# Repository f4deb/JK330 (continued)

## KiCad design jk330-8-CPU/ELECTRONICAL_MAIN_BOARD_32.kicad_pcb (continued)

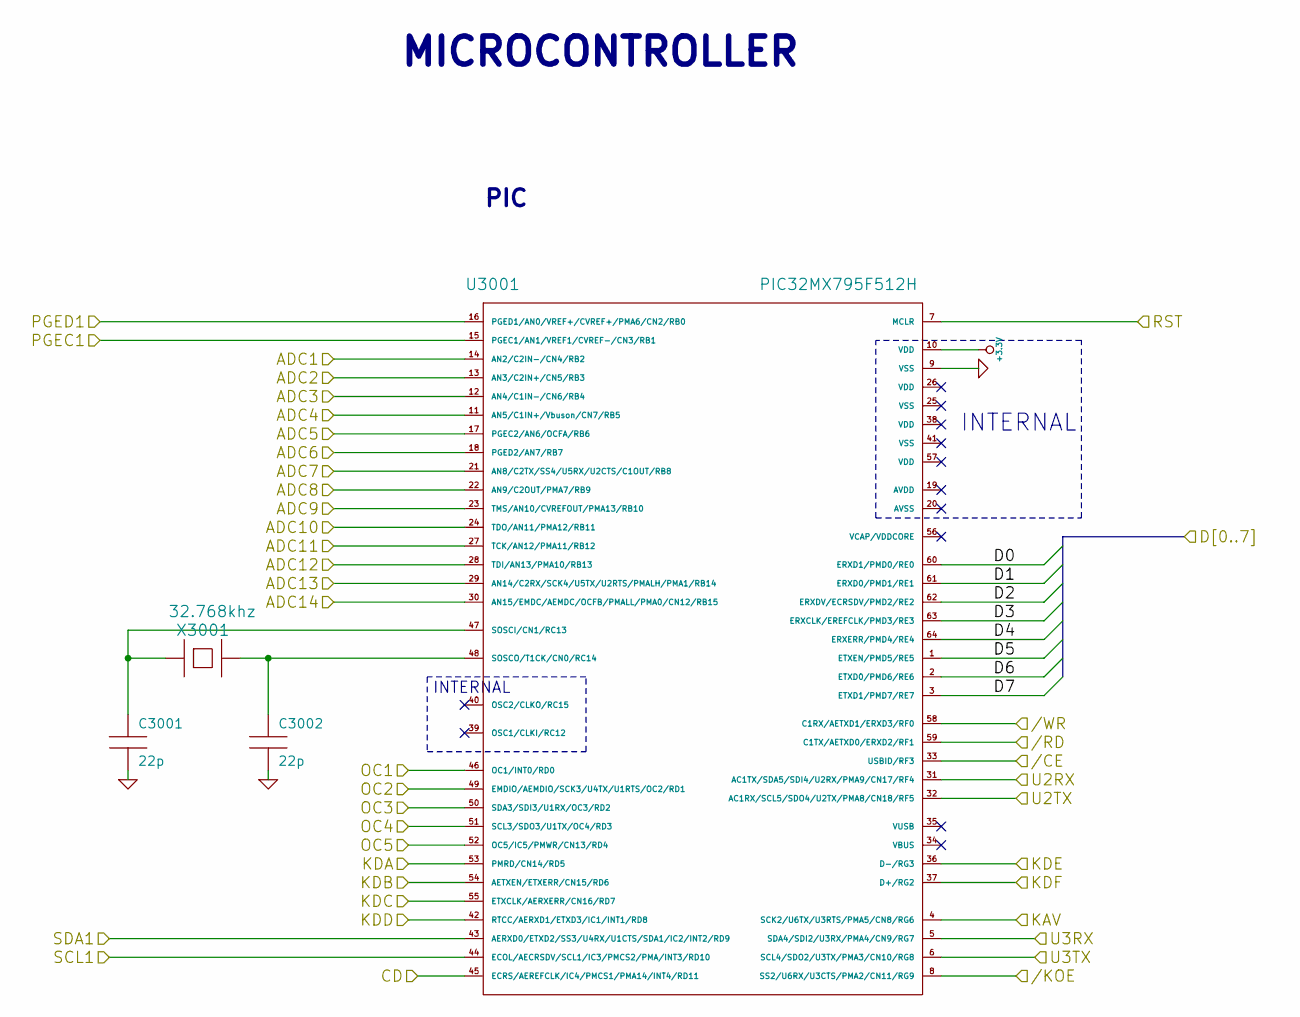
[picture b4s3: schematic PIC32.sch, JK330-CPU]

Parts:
C3001, C3002: 22p
U3001: PIC32MX795F512H
X3001: 32.768khz

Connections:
+3.3V: U3001.10 (VDD); also elsewhere on the board
/5vto3v3//CE: U3001.33 (USBID/RF3); also elsewhere on the board
/5vto3v3//KOE: U3001.8 (SS2/U6RX/U3CTS/PMA2/CN11/RG9); also elsewhere on the board
/5vto3v3//RD: U3001.59 (C1TX/AETXD0/ERXD2/RF1); also elsewhere on the board
/5vto3v3//WR: U3001.58 (C1RX/AETXD1/ERXD3/RF0); also elsewhere on the board
/5vto3v3/CD: U3001.45 (ECRS/AEREFCLK/IC4/PMCS1/PMA14/INT4/RD11); also elsewhere on the board
/5vto3v3/D0: U3001.60 (ERXD1/PMD0/RE0); also elsewhere on the board
/5vto3v3/D1: U3001.61 (ERXD0/PMD1/RE1); also elsewhere on the board
/5vto3v3/D2: U3001.62 (ERXDV/ECRSDV/PMD2/RE2); also elsewhere on the board
/5vto3v3/D3: U3001.63 (ERXCLK/EREFCLK/PMD3/RE3); also elsewhere on the board
/5vto3v3/D4: U3001.64 (ERXERR/PMD4/RE4); also elsewhere on the board
/5vto3v3/D5: U3001.1 (ETXEN/PMD5/RE5); also elsewhere on the board
/5vto3v3/D6: U3001.2 (ETXD0/PMD6/RE6); also elsewhere on the board
/5vto3v3/D7: U3001.3 (ETXD1/PMD7/RE7); also elsewhere on the board
/5vto3v3/KAV: U3001.4 (SCK2/U6TX/U3RTS/PMA5/CN8/RG6); also elsewhere on the board
/5vto3v3/KDA: U3001.53 (PMRD/CN14/RD5); also elsewhere on the board
/5vto3v3/KDB: U3001.54 (AETXEN/ETXERR/CN15/RD6); also elsewhere on the board
/5vto3v3/KDC: U3001.55 (ETXCLK/AERXERR/CN16/RD7); also elsewhere on the board
/5vto3v3/KDD: U3001.42 (RTCC/AERXD1/ETXD3/IC1/INT1/RD8); also elsewhere on the board
/5vto3v3/KDE: U3001.36 (D-/RG3); also elsewhere on the board
/5vto3v3/KDF: U3001.37 (D+/RG2); also elsewhere on the board
/5vto3v3/OC1: U3001.46 (OC1/INT0/RD0); also elsewhere on the board
/5vto3v3/OC2: U3001.49 (EMDIO/AEMDIO/SCK3/U4TX/U1RTS/OC2/RD1); also elsewhere on the board
/5vto3v3/OC3: U3001.50 (SDA3/SDI3/U1RX/OC3/RD2); also elsewhere on the board
/5vto3v3/OC4: U3001.51 (SCL3/SDO3/U1TX/OC4/RD3); also elsewhere on the board
/5vto3v3/OC5: U3001.52 (OC5/IC5/PMWR/CN13/RD4); also elsewhere on the board
/5vto3v3/SCL1: U3001.44 (ECOL/AECRSDV/SCL1/IC3/PMCS2/PMA/INT3/RD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); also elsewhere on the board
/5vto3v3/SDA1: U3001.43 (AERXD0/ETXD2/SS3/U4RX/U1CTS/SDA1/IC2/IN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); also elsewhere on the board
/5vto3v3/U2RX: U3001.31 (AC1TX/SDA5/SDI4/U2RX/PMA9/CN17/RF4); also elsewhere on the board
/5vto3v3/U2TX: U3001.32 (AC1RX/SCL5/SDO4/U2TX/PMA8/CN18/RF5); also elsewhere on the board
/5vto3v3/U3RX: U3001.5 (SDA4/SDI2/U3RX/PMA4/CN9/RG7); also elsewhere on the board
/5vto3v3/U3TX: U3001.6 (SCL4/SDO2/U3TX/PMA3/CN10/RG8); also elsewhere on the board
/PIC32/ADC1: U3001.14 (AN2/C2IN-/CN4/RB2); also elsewhere on the board
/PIC32/ADC2: U3001.13 (AN3/C2IN+/CN5/RB3); also elsewhere on the board
/PIC32/ADC3: U3001.12 (AN4/C1IN-/CN6/RB4); also elsewhere on the board
/PIC32/ADC4: U3001.11 (AN5/C1IN+/Vbuson/CN7/RB5); also elsewhere on the board
/PIC32/ADC5: U3001.17 (PGEC2/AN6/OCFA/RB6); also elsewhere on the board
/PIC32/ADC6: U3001.18 (PGED2/AN7/RB7); also elsewhere on the board
/PIC32/ADC7: U3001.21 (AN8/C2TX/SS4/U5RX/U2CTS/C1OUT/RB8); also elsewhere on the board
/PIC32/ADC8: U3001.22 (AN9/C2OUT/PMA7/RB9); also elsewhere on the board
/PIC32/ADC9: U3001.23 (TMS/AN10/CVREFOUT/PMA13/RB10); also elsewhere on the board
/PIC32/ADC10: U3001.24 (TDO/AN11/PMA12/RB11); also elsewhere on the board
/PIC32/ADC11: U3001.27 (TCK/AN12/PMA11/RB12); also elsewhere on the board
/PIC32/ADC12: U3001.28 (TDI/AN13/PMA10/RB13); also elsewhere on the board
/PIC32/ADC13: U3001.29 (AN14/C2RX/SCK4/U5TX/U2RTS/PMALH/PMA1/RB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); also elsewhere on the board
/PIC32/ADC14: U3001.30 (AN15/EMDC/AEMDC/OCFB/PMALL/PMA0/CN12/RB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); also elsewhere on the board
/PIC32/PGEC1: U3001.15 (PGEC1/AN1/VREF1/CVREF-/CN3/RB1); also elsewhere on the board
/PIC32/PGED1: U3001.16 (PGED1/AN0/VREF+/CVREF+/PMA6/CN2/RB0); also elsewhere on the board
/PIC32/RST: U3001.7 (MCLR); also elsewhere on the board
GND: C3001.2, C3002.2, U3001.9 (VSS); also elsewhere on the board
unnamed: C3002.1, U3001.48 (SOSCO/T1CK/CN0/RC14), X3001.2
unnamed: C3001.1, U3001.47 (SOSCI/CN1/RC13), X3001.1

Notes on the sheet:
INTERNAL
MICROCONTROLLER
PIC

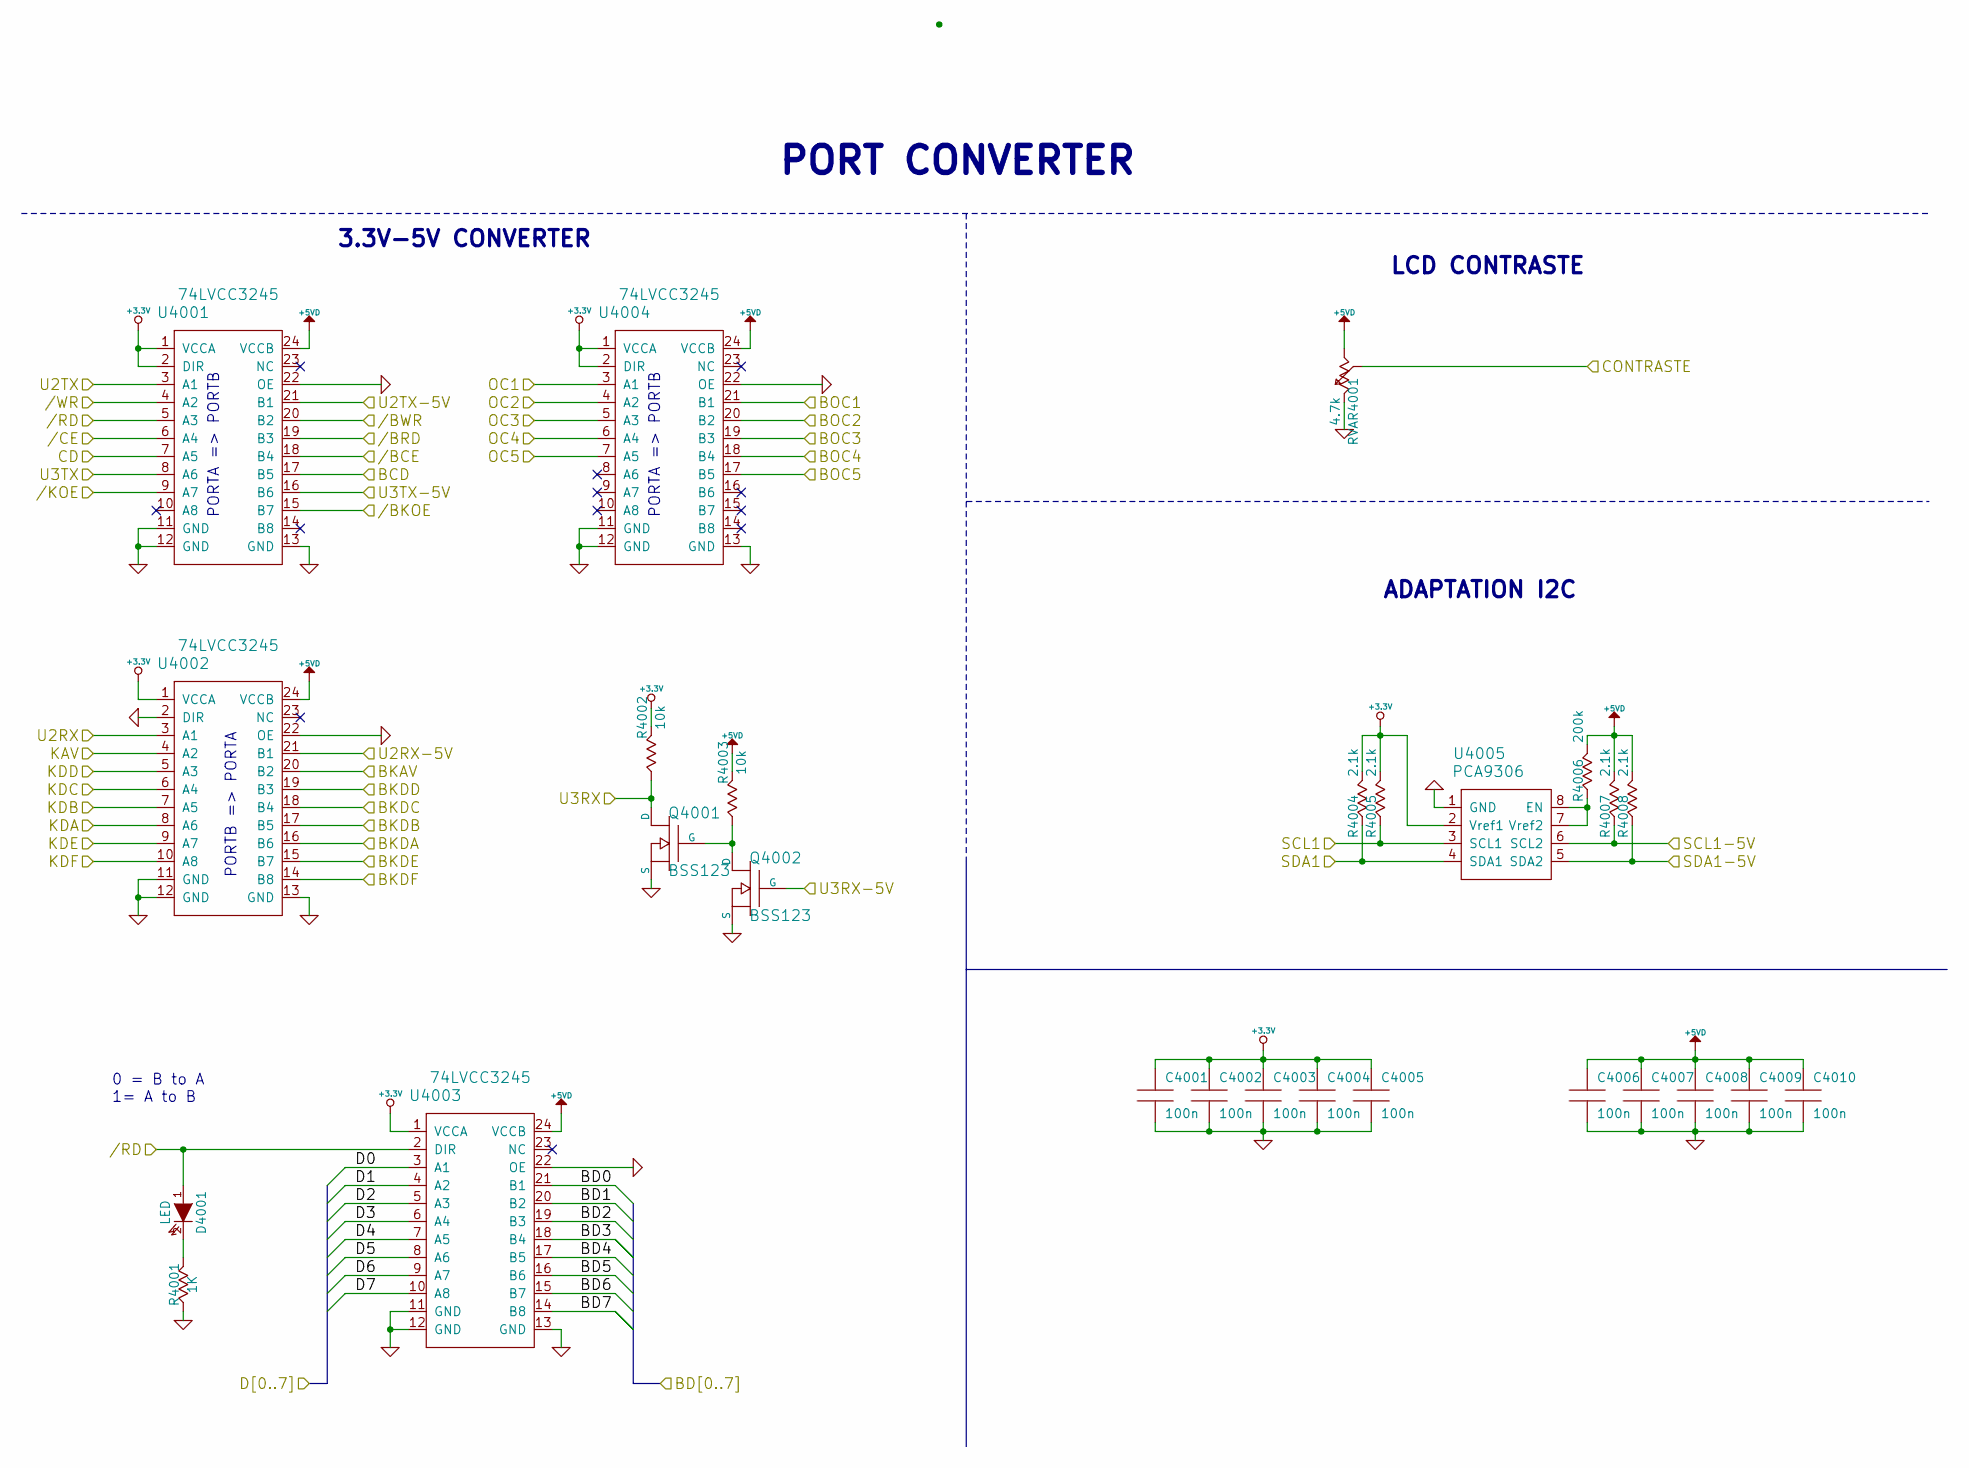
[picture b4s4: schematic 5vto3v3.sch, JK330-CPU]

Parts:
C4001, C4002, C4003, C4004, C4005, C4006, C4007, C4008, C4009, C4010: 100n
D4001: LED
Q4001, Q4002: BSS123
R4001: 1K
R4002, R4003: 10k
R4004, R4005, R4007, R4008: 2.1k
R4006: 200k
RVAR4001: 4.7k
U4001, U4002, U4003, U4004: 74LVCC3245
U4005: PCA9306

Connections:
+3.3V: C4001.1, C4002.1, C4003.1, C4004.1, C4005.1, R4002.1, R4004.1, R4005.1, U4001.1 (VCCA), U4001.2 (DIR), U4002.1 (VCCA), U4003.1 (VCCA), U4004.1 (VCCA), U4004.2 (DIR), U4005.2 (Vref1); also elsewhere on the board
+5VD: C4006.1, C4007.1, C4008.1, C4009.1, C4010.1, R4003.1, R4006.1, R4007.1, R4008.1, RVAR4001.2, U4001.24 (VCCB), U4002.24 (VCCB), U4003.24 (VCCB), U4004.24 (VCCB); also elsewhere on the board
/5vto3v3//BCE: U4001.18 (B4); also elsewhere on the board
/5vto3v3//BKOE: U4001.15 (B7); also elsewhere on the board
/5vto3v3//BRD: U4001.19 (B3); also elsewhere on the board
/5vto3v3//BWR: U4001.20 (B2); also elsewhere on the board
/5vto3v3//CE: U4001.6 (A4); also elsewhere on the board
/5vto3v3//KOE: U4001.9 (A7); also elsewhere on the board
/5vto3v3//RD: D4001.1 (A), U4001.5 (A3), U4003.2 (DIR); also elsewhere on the board
/5vto3v3//WR: U4001.4 (A2); also elsewhere on the board
/5vto3v3/BCD: U4001.17 (B5); also elsewhere on the board
/5vto3v3/BKAV: U4002.20 (B2); also elsewhere on the board
/5vto3v3/BKDA: U4002.16 (B6); also elsewhere on the board
/5vto3v3/BKDB: U4002.17 (B5); also elsewhere on the board
/5vto3v3/BKDC: U4002.18 (B4); also elsewhere on the board
/5vto3v3/BKDD: U4002.19 (B3); also elsewhere on the board
/5vto3v3/BKDE: U4002.15 (B7); also elsewhere on the board
/5vto3v3/BKDF: U4002.14 (B8); also elsewhere on the board
/5vto3v3/BOC1: U4004.21 (B1); also elsewhere on the board
/5vto3v3/BOC2: U4004.20 (B2); also elsewhere on the board
/5vto3v3/BOC3: U4004.19 (B3); also elsewhere on the board
/5vto3v3/BOC4: U4004.18 (B4); also elsewhere on the board
/5vto3v3/BOC5: U4004.17 (B5); also elsewhere on the board
/5vto3v3/CD: U4001.7 (A5); also elsewhere on the board
/5vto3v3/CONTRASTE: RVAR4001.3; also elsewhere on the board
/5vto3v3/D0: U4003.3 (A1); also elsewhere on the board
/5vto3v3/D1: U4003.4 (A2); also elsewhere on the board
/5vto3v3/D2: U4003.5 (A3); also elsewhere on the board
/5vto3v3/D3: U4003.6 (A4); also elsewhere on the board
/5vto3v3/D4: U4003.7 (A5); also elsewhere on the board
/5vto3v3/D5: U4003.8 (A6); also elsewhere on the board
/5vto3v3/D6: U4003.9 (A7); also elsewhere on the board
/5vto3v3/D7: U4003.10 (A8); also elsewhere on the board
/5vto3v3/KAV: U4002.4 (A2); also elsewhere on the board
/5vto3v3/KDA: U4002.8 (A6); also elsewhere on the board
/5vto3v3/KDB: U4002.7 (A5); also elsewhere on the board
/5vto3v3/KDC: U4002.6 (A4); also elsewhere on the board
/5vto3v3/KDD: U4002.5 (A3); also elsewhere on the board
/5vto3v3/KDE: U4002.9 (A7); also elsewhere on the board
/5vto3v3/KDF: U4002.10 (A8); also elsewhere on the board
/5vto3v3/OC1: U4004.3 (A1); also elsewhere on the board
/5vto3v3/OC2: U4004.4 (A2); also elsewhere on the board
/5vto3v3/OC3: U4004.5 (A3); also elsewhere on the board
/5vto3v3/OC4: U4004.6 (A4); also elsewhere on the board
/5vto3v3/OC5: U4004.7 (A5); also elsewhere on the board
/5vto3v3/SCL1: R4005.2, U4005.3 (SCL1); also elsewhere on the board
/5vto3v3/SDA1: R4004.2, U4005.4 (SDA1); also elsewhere on the board
/5vto3v3/U2RX: U4002.3 (A1); also elsewhere on the board
/5vto3v3/U2RX-5V: U4002.21 (B1); also elsewhere on the board
/5vto3v3/U2TX: U4001.3 (A1); also elsewhere on the board
/5vto3v3/U2TX-5V: U4001.21 (B1); also elsewhere on the board
/5vto3v3/U3RX: Q4001.3 (D), R4002.2; also elsewhere on the board
/5vto3v3/U3RX-5V: Q4002.2 (G); also elsewhere on the board
/5vto3v3/U3TX: U4001.8 (A6); also elsewhere on the board
/5vto3v3/U3TX-5V: U4001.16 (B6); also elsewhere on the board
/BD0: U4003.21 (B1); also elsewhere on the board
/BD1: U4003.20 (B2); also elsewhere on the board
/BD2: U4003.19 (B3); also elsewhere on the board
/BD3: U4003.18 (B4); also elsewhere on the board
/BD4: U4003.17 (B5); also elsewhere on the board
/BD5: U4003.16 (B6); also elsewhere on the board
/BD6: U4003.15 (B7); also elsewhere on the board
/BD7: U4003.14 (B8); also elsewhere on the board
/INTERFACE BOARD/SCL: R4007.2, U4005.6 (SCL2); also elsewhere on the board
/INTERFACE BOARD/SDA: R4008.2, U4005.5 (SDA2); also elsewhere on the board
GND: C4001.2, C4002.2, C4003.2, C4004.2, C4005.2, C4006.2, C4007.2, C4008.2, C4009.2, C4010.2, Q4001.1 (S), Q4002.1 (S), R4001.2, RVAR4001.1, U4001.11 (GND), U4001.12 (GND), U4001.13 (GND), U4001.22 (OE), U4002.2 (DIR), U4002.11 (GND), U4002.12 (GND), U4002.13 (GND), U4002.22 (OE), U4003.11 (GND), U4003.12 (GND), U4003.13 (GND), U4003.22 (OE), U4004.11 (GND), U4004.12 (GND), U4004.13 (GND), U4004.22 (OE), U4005.1 (GND); also elsewhere on the board
unnamed: Q4001.2 (G), Q4002.3 (D), R4003.2
unnamed: R4006.2, U4005.7 (Vref2), U4005.8 (EN)
unnamed: D4001.2 (K), R4001.1

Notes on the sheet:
ADAPTATION I2C
PORTA => PORTB
LCD CONTRASTE
0 = B to A 1= A to B
3.3V-5V CONVERTER
PORT CONVERTER
PORTB => PORTA

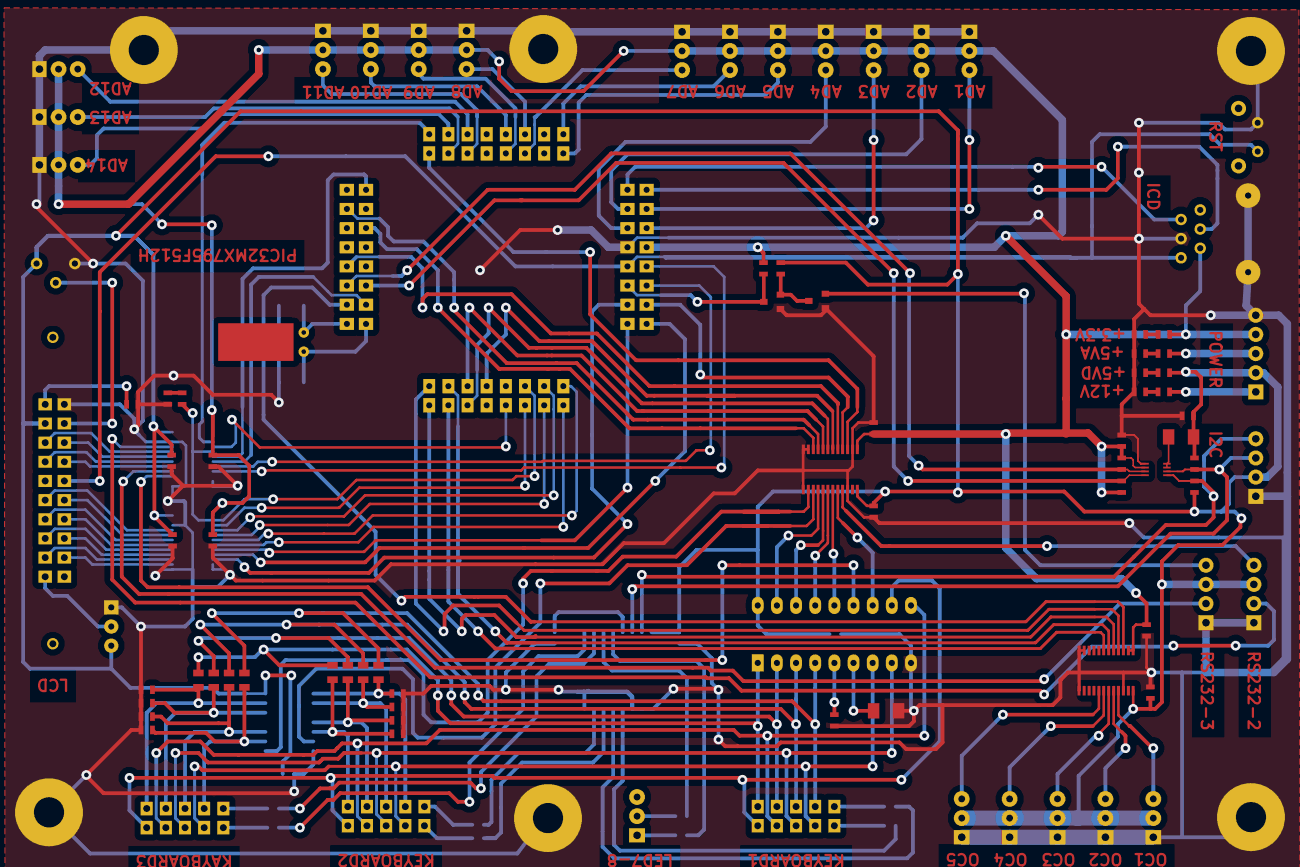
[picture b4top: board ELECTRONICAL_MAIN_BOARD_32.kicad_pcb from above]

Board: 2 copper layers, 110 parts (0 on the bottom side), 131 nets.

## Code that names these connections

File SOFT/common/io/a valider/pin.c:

#include <p30fxxxx.h>

#include "pin.h"

#include "../../common/commons.h"
#include "../../common/error/error.h"

#include "../../common/io/printWriter.h"
#include "../../common/io/outputStream.h"

#include "../../common/log/logger.h"
#include "../../common/log/logLevel.h"

void setPinValue(int pinIndex, BOOL pinValue) {
    switch (pinIndex) {
            // PORT B
        case PIN_INDEX_RB0: LATBbits.LATB0 = pinValue;
            break;
        case PIN_INDEX_RB1: LATBbits.LATB1 = pinValue;
            break;
        case PIN_INDEX_RB2: LATBbits.LATB2 = pinValue;
            break;
        case PIN_INDEX_RB3: LATBbits.LATB3 = pinValue;
            break;
        case PIN_INDEX_RB4: LATBbits.LATB4 = pinValue;
            break;
        case PIN_INDEX_RB5: LATBbits.LATB5 = pinValue;
            break;
        case PIN_INDEX_RB6: LATBbits.LATB6 = pinValue;
            break;
        case PIN_INDEX_RB7: LATBbits.LATB7 = pinValue;
            break;
        case PIN_INDEX_RB8: LATBbits.LATB8 = pinValue;
            break;
        case PIN_INDEX_RB9: LATBbits.LATB9 = pinValue;
            break;
        case PIN_INDEX_RB10: LATBbits.LATB10 = pinValue;
            break;
        case PIN_INDEX_RB11: LATBbits.LATB11 = pinValue;
            break;
        case PIN_INDEX_RB12: LATBbits.LATB12 = pinValue;
            break;

            // PORT C
        case PIN_INDEX_RC13: LATCbits.LATC13 = pinValue;
            break;
        case PIN_INDEX_RC14: LATCbits.LATC14 = pinValue;
            break;
        case PIN_INDEX_RC15: LATCbits.LATC15 = pinValue;
            break;

            // PORT D
        case PIN_INDEX_RD0: LATDbits.LATD0 = pinValue;
            break;
        case PIN_INDEX_RD1: LATDbits.LATD1 = pinValue;
            break;
        case PIN_INDEX_RD2: LATDbits.LATD2 = pinValue;
            break;
        case PIN_INDEX_RD3: LATDbits.LATD3 = pinValue;
            break;
        case PIN_INDEX_RD8: LATDbits.LATD8 = pinValue;
            break;
        case PIN_INDEX_RD9: LATDbits.LATD9 = pinValue;
            break;

            // PORT A
        case PIN_INDEX_RA11: LATAbits.LATA11 = pinValue;
            break;

            // PORT F
        case PIN_INDEX_RF0: LATFbits.LATF0 = pinValue;
            break;
        case PIN_INDEX_RF6: LATFbits.LATF6 = pinValue;
            break;

        default:
        {
            writeError(IO_PIN_INDEX_ERROR);
        }
    }

}

BOOL getPinValue(int pinIndex) {
    switch (pinIndex) {
            // PORT B
        case PIN_INDEX_RB0: return PORTBbits.RB0;
        case PIN_INDEX_RB1: return PORTBbits.RB1;
        case PIN_INDEX_RB2: return PORTBbits.RB2;
        case PIN_INDEX_RB3: return PORTBbits.RB3;
        case PIN_INDEX_RB4: return PORTBbits.RB4;
        case PIN_INDEX_RB5: return PORTBbits.RB5;
        case PIN_INDEX_RB6: return PORTBbits.RB6;
        case PIN_INDEX_RB7: return PORTBbits.RB7;
        case PIN_INDEX_RB8: return PORTBbits.RB8;
        case PIN_INDEX_RB9: return PORTBbits.RB9;
        case PIN_INDEX_RB10: return PORTBbits.RB10;
        case PIN_INDEX_RB11: return PORTBbits.RB11;
        case PIN_INDEX_RB12: return PORTBbits.RB12;

            // PORT C
        case PIN_INDEX_RC13: return PORTCbits.RC13;
        case PIN_INDEX_RC14: return PORTCbits.RC14;
        case PIN_INDEX_RC15: return PORTCbits.RC15;

            // PORT D
        case PIN_INDEX_RD0: return PORTDbits.RD0;
        case PIN_INDEX_RD1: return PORTDbits.RD1;
        case PIN_INDEX_RD2: return PORTDbits.RD2;
        case PIN_INDEX_RD3: return PORTDbits.RD3;
        case PIN_INDEX_RD8: return PORTDbits.RD8;
        case PIN_INDEX_RD9: return PORTDbits.RD9;

            // PORT A
        case PIN_INDEX_RA11: return PORTAbits.RA11;

            // PORTF
        case PIN_INDEX_RF0: return PORTFbits.RF0;
        case PIN_INDEX_RF6: return PORTFbits.RF6;
    }
    writeError(IO_PIN_INDEX_ERROR);

    // log the error
    return FALSE;
}

void printAllPinValues(OutputStream* outputStream) {
    int i = 0;
    for (i = PIN_MIN_INDEX; i <= PIN_MAX_INDEX; i++) {
        BOOL value = getPinValue(i);
        appendString(outputStream, "Pin ");
        appendHex2(outputStream, i);
        append(outputStream, '=');
        appendBOOL(outputStream, value);
        println(outputStream);
    }
}

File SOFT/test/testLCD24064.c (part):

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// Afficheur graphique 

#define bus_LCD	PORTE
#define wr_LCD	PORTFbits.RF0
#define rd_LCD	PORTFbits.RF1
#define ce_LCD	PORTFbits.RF3
#define cd_LCD 	PORTDbits.RD11


#define ad_base_graph 0x0200
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
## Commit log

2013-04-28 Création du repos carteJK330-1-BF
2013-04-28 correction bf996 schema
2013-04-28 Ajout doc technique
2013-04-29 MAJ composants
2013-04-30 Rajout commande PTT
    +12VTV
    +12VRX
2013-05-10 MAJ Façade
2013-05-10 MAJ SCHEMA FONCTIONNEL
2013-05-20 maj EMPREINTE
2013-06-04 MAJ mineur
2013-06-04 MAJ +AJOUT SBL 3D
2013-06-09 Routage PCB
2013-06-11 Reste 2 pistes a router
2013-06-16 Fin PCB
2013-06-18 Fin Routage PCb V0-10
2013-06-24 MAJ3D
2013-06-25 MAJ DOC DTS
2013-07-03 LED CMS X4 12V
2013-08-03 Ajout carte power
2013-08-21 POWER
2013-08-27 MAJ mineur
2013-08-29 POWER PCB OK
2013-08-29 MAJ TEXTE PCB
2013-08-31 MAJ pour impression
2013-08-31 MAJ EMPREINTE SELF
2013-09-16 DEBUT CPU
2013-09-17 MAJ DOC TECHNIQUE
2013-09-21 MAJ CPU
2013-09-23 SCHEMA CPU 85%
2013-09-24 CPU SCHEMA 100%
2013-11-04 CPU EN TEST
2013-11-30 LCD HD77480
2013-12-09 DEBUT SOFT
    La base electronique est operationnel.
2013-12-09 debut soft
    La base electronique est operationnel
2014-02-02 MISE EN FORME
2014-02-02 INIT OUTPUTSTREAM UART OK
2014-05-20 TEST AJOUT PCF8573
2014-05-20 AJOUT CARTE PCF8574
2014-05-20 BF BOARD UPDATE
2014-05-20 UPDATE INTERFACE SON
2014-05-20 UPDATE LED 4x
2014-05-20 SOFT HORLOGE LCD PCF8574 PCF8573 OK
2014-05-20 TEST ERASE
2014-05-25 MAJ MOTOR
2014-05-26 MAJ SOFT CODER
2014-05-27 DEBUT SEQUENCE TEST MOTOR_BOARD_32
2014-06-02 AUTOTEST MOTOR BOARD READY manque IO et CAN
2014-06-14 MODIF PROG TEST MOTOR BOARD
2014-08-09 AJOUT PCF8563 R/W OK
2014-08-09 test EEPROM I2C NOK En cours
2014-08-10 ADD EEPROM_I2C rest probleme de lecture de plusieurs octets
2017-03-22 MAJ???
